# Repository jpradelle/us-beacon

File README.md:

# Ultrasonic indoor positioning system
This project contains electronic card design and software to build an indoor 2D positioning system based on ultrasonic 
emitters and receivers with Time Difference Of Arrival (TDOA) algorithm to determine position.

## Context
This project has been made during French Robotic Cup which takes place in european Eurobot contest. During this contest,
2 teams are playing one against the other, with one or two bots, to achieve some objectives, on a game table of 2 per 3
meters. Bots must not enter in collision with other team bots, purpose of this project is to determine quite precisely
position of 2 opponent bots.

Contest rules allow to place 3 fixed beacons on dedicated table places which will be called receivers, and a 
80mm\*80mm\*80mm beacon on each opponent bot which will be called emitters.

See [contest rules](doc/E2017_Rules_EN.pdf) for more details.

### Extra considerations
* Due to intensive usage of 40kHz ultrasonic modules by other teams, we avoided use of 40kHz frequency.
* To avoid possible interference with other teams, a sort of "modulation" have been implemented.
* Using low frequency ultrasonic transceivers and receivers allow to emit/receive on a wide angle.

## Principle
An emitter is placed on opponent bot, emitter will emit every 75ms a signal over 360°. One of the three fixed receivers
will receive the signal first at time reference T. Due to slow speed of sound, the 2nd receives a bit later at T + dt1,
and the 3rd later next at T + dt2. Knowing speed of sound, dt1 and dt2 can be converted to distance dr1 and dr2. With
only dr1 and dr2 and a Time Difference Of Arrival (TDOA) algorithm, we can compute position of emitter on a plan.

R is unknown, only dr1 and dr2 are determined by the system.

## System accuracy
TODO

## Architecture
Project is made of following parts.

### 2 emitters
One working with 25kHz frequency, one with 32.8kHz frequency. Emitters are made of:
* 1 9V battery
* 1 ATtiny45 microcontroller for pulse generation
* 4 ultrasonic transceivers
* some electronic for power supply, H bridge to run transceivers, ...

### 3 receivers
Each receiver beacon is made with one cards to receive 25kHz another one to receive 32.8kHz signals with 2 or 3
ultrasonic receivers.

Each ultrasonic receiver is made of
* 1 ultrasonic receiver
* 1 4 channels TLO74CN Operational Amplifier
* Some resistors, capacitors and schottky diodes for signal amplification and filtering
* 1 ATtiny45 for reading analog input and building a simple HIGH signal when ultrasonic signal is received

It contains also a power card which ensure different power conversions and aggregate demodulated signals from receivers,
made of:
* 2 9V battery
* 1 12V NCP1117DT12RKG convertor
* 1 5V R-78E5.0-0.5 convertor
* 1 3.3 LP2950ACDT-3.3RG convertor (for receiver beacon 1 only)
* Few connectors

#### Receiver 1
Contains 1 power card, 1 card with 2 receiver channels of 25kHz and 1 card with 2 receiver channels of 32.8kHz.

It also contains 1 RF card, which receive all numerical signals produced by receivers channels, compute TDOA algorithm
and send position by serial to RF module. It is made of:
* 1 Teensy 3.2 micro controller
* 1 RFBee (or 1 ESP8266, extra adaptor card needed)
* Few 3.3V zener diodes and schottky diodes
* Few connectors

#### Receiver 2
Contains 1 power card, 1 card with 2 receiver channels of 25kHz and 1 card with 2 receiver channels of 32.8kHz.

#### Receiver 3
Contains 1 power card, 1 card with 3 receiver channels of 25kHz and 1 card with 3 receiver channels of 32.8kHz.

## Folder structure of project
### Simulation
[simu](simu) folder contains some simulations for testing different TOA and TDOA algorithms.
See [simu/README.md](simu/README.md) for more details of algorithms performances.

### Electronics
[elec](elec) folder contains electronic designs of one 25kHz emitter, one 32.8kHz emitter, 3 receivers of 25kHz and
32.8kHz, and other power cards. See [elec/README.md](elec/README.md) for more information.

### Code
[code](code) folder contains code of all microcontroller used in this project. See [code/README.md](code/README.md) for
more information.

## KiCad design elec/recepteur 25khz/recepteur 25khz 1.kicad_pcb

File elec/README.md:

# Electronic
This folder contains needed electronics schema made with Kicad software for building working solution for 2 bots
positioning.

## Kicad projects
### 25kHz emitter
Electronic schematics and PCB drawings are made in [emetteur 25khz](emetteur%2025khz) project.

PDF schematics [here](../doc/elec/25khz_emitter_schematics.pdf)

### 32.8kHz emitter
Electronic schematics and PCB drawings are made in [emetteur 32khz](emetteur%2032khz) project.

PDF schematics [here](../doc/elec/32khz_emitter_schematics.pdf)

### 3 sets of 25kHz receivers
Electronic schematics and PCB drawings are made in [recepteur 25khz](recepteur%2025khz) project.

PDF schematics [here](../doc/elec/25khz_receiver_schematics.pdf)

Project contains stuff for building 2 fixed receiving beacons made of 2 ultrasonic receivers and 1 fixed receiving
beacon made of 3 ultrasonic receivers.

This projects contains other cards, see after.

### 3 sets of 32.8kHz receivers
Electronic schematics and PCB drawings are made in [recepteur 32khz](recepteur%2032khz) project.

PDF schematics [here](../doc/elec/32khz_receiver_schematics.pdf)

Project contains stuff for building 2 fixed receiving beacons made of 2 ultrasonic receivers and 1 fixed receiving
beacon made of 3 ultrasonic receivers.

### 3 power cards
Electronic schematics and PCB drawings are made in [recepteur 25khz](recepteur%2025khz) project.

Those 3 power cards are made for powering receiving cards and aggregating receiving cards signal to output them on one
connector.

### RF card
Electronic schematics and PCB drawings are made in [recepteur 25khz](recepteur%2025khz) project.

This RF card made for running TDOA algorithm with signals given from 3 power cards on a teensy microcontroller, found
position is expected to be transmitted by serial to RF card.

## Bill Of Material
### 25kHz emitter
| Item         | Qty | Reference(s)                                                            | RadioSpares ref    |
|--------------|-----|-------------------------------------------------------------------------|--------------------|
| 100n         | 1   | C1                                                                      | 264-4416           |
| LED          | 1   | D1                                                                      |                    |
| ATTINY45-P   | 1   | IC1                                                                     | 696-2614           |
| CONN_2       | 5   | P1, P3, P4, P5, P6                                                      | 163-5303, 163-5305 |
| 2N3904       | 8   | Q1, Q4, Q5, Q7, Q9, Q12, Q14, Q16                                       | 739-0397           |
| 2N3906       | 8   | Q2, Q3, Q6, Q8, Q10, Q11, Q13, Q15                                      | 739-0375           |
| 22k          | 16  | R1, R2, R4, R5, R7, R8, R9, R10, R11, R12, R16, R17, R18, R19, R20, R21 | 740-9016           |
| 1k           | 5   | R3, R6, R13, R14, R15                                                   | 740-8971           |
| 10k          | 1   | R22                                                                     | 740-9072           |
| R-78E5.0-0.5 | 1   | REGUL1                                                                  | 757-7239           |
| SWITCH       | 1   | U1                                                                      | 734-7315           |

+ 4 25kHz Ultrasonic transmitters

### 32.8kHz emitter
| Item         | Qty | Reference(s)                                                            | RadioSpares ref    |
|--------------|-----|-------------------------------------------------------------------------|--------------------|
| 100n         | 1   | C1                                                                      | 264-4416           |
| LED          | 1   | D1                                                                      |                    |
| ATTINY45-P   | 1   | IC1                                                                     | 696-2614           |
| CONN_2       | 5   | P1, P3, P4, P5, P6                                                      | 163-5303, 163-5305 |
| 2N3904       | 8   | Q1, Q4, Q5, Q7, Q9, Q12, Q14, Q16                                       | 739-0397           |
| 2N3906       | 8   | Q2, Q3, Q6, Q8, Q10, Q11, Q13, Q15                                      | 739-0375           |
| 22k          | 16  | R1, R2, R4, R5, R7, R8, R9, R10, R11, R12, R16, R17, R18, R19, R20, R21 | 740-9016           |
| 1k           | 5   | R3, R6, R13, R14, R15                                                   | 740-8971           |
| 10k          | 1   | R22                                                                     | 740-9072           |
| R-78E5.0-0.5 | 1   | REGUL1                                                                  | 757-7239           |
| SWITCH       | 1   | U1                                                                      | 734-7315           |

+ 4 32.8kHz Ultrasonic transmitters

### 25kHz receivers + power cards + RF card
| Value            | Qty | Reference(s)                                                                                                                                                                                            | RadioSpares ref    |
|------------------|-----|---------------------------------------------------------------------------------------------------------------------------------------------------------------------------------------------------------|--------------------|
| 10n              | 14  | C1, C5, C12, C16, C23, C27, C34, C38, C45, C49, C56, C60, C67, C71                                                                                                                                      | 264-4371           |
| 470p             | 14  | C2, C8, C13, C19, C24, C30, C35, C41, C46, C52, C57, C63, C68, C74                                                                                                                                      | 264-4315           |
| 47n              | 14  | C3, C4, C14, C15, C25, C26, C36, C37, C47, C48, C58, C59, C69, C70                                                                                                                                      | 147-998            |
| 100n             | 21  | C6, C7, C11, C17, C18, C22, C28, C29, C33, C39, C40, C44, C50, C51, C55, C61, C62, C66, C72, C73, C77                                                                                                   | 264-4416           |
| 1n               | 14  | C9, C10, C20, C21, C31, C32, C42, C43, C53, C54, C64, C65, C75, C76                                                                                                                                     | 264-4337           |
| 10µ              | 6   | C78, C79, C80, C81, C82, C83                                                                                                                                                                            | 440-6553           |
| 1µ               | 1   | C84                                                                                                                                                                                                     |                    |
| DIODESCH         | 42  | D1, D2, D3, D4, D5, D6, D7, D8, D9, D10, D11, D12, D13, D14, D15, D16, D17, D18, D19, D20, D21, D22, D23, D24, D25, D26, D27, D28, D39, D41, D43, D45, D47, D49, D51, D53, D55, D57, D59, D61, D63, D65 | 743-5894           |
| LED              | 10  | D29, D30, D31, D32, D33, D34, D35, D36, D37, D38                                                                                                                                                        |                    |
| ZENER            | 14  | D40, D42, D44, D46, D48, D50, D52, D54, D56, D58, D60, D62, D64, D66                                                                                                                                    | 710-4216           |
| ATTINY45-P       | 7   | IC1, IC2, IC3, IC4, IC5, IC6, IC7                                                                                                                                                                       | 696-2614           |
| TEENSY           | 1   | IC8                                                                                                                                                                                                     |                    |
| CONN_3           | 1   | K1                                                                                                                                                                                                      | 163-5303, 163-5305 |
| CONN_6           | 6   | P1, P4, P5, P8, P10, P17                                                                                                                                                                                | 163-5303, 163-5305 |
| CONN_2           | 6   | P2, P3, P6, P7, P12, P13                                                                                                                                                                                | 163-5303, 163-5305 |
| CONN_5           | 2   | P9, P19                                                                                                                                                                                                 | 163-5303, 163-5305 |
| CONN_7           | 7   | P11, P14, P15, P16, P18, P20, P21                                                                                                                                                                       | 163-5303, 163-5305 |
| CONN_4           | 1   | P22                                                                                                                                                                                                     | 163-5303, 163-5305 |
| 1k               | 21  | R1, R2, R5, R11, R12, R13, R14, R17, R27, R33, R34, R37, R45, R46, R49, R55, R56, R59, R65, R66, R69                                                                                                    | 740-8971           |
| 10k              | 37  | R3, R4, R8, R15, R16, R20, R23, R24, R25, R26, R30, R35, R36, R40, R43, R44, R47, R48, R52, R57, R58, R62, R67, R68, R72, R75, R76, R77, R78, R79, R80, R81, R82, R83, R84, R85, R86                    | 740-9072           |
| 47k              | 28  | R6, R7, R9, R10, R18, R19, R21, R22, R28, R29, R31, R32, R38, R39, R41, R42, R50, R51, R53, R54, R60, R61, R63, R64, R70, R71, R73, R74                                                                 | 740-9035           |
| 2.2k             | 14  | R87, R88, R89, R90, R91, R92, R93, R94, R95, R96, R97, R98, R99, R100                                                                                                                                   | 810-1750           |
| RFBEE            | 1   | RF1                                                                                                                                                                                                     |                    |
| TL074            | 7   | U1, U2, U3, U4, U9, U10, U11                                                                                                                                                                            | 302-621            |
| R-78E5.0-0.5     | 3   | U5, U7, U12                                                                                                                                                                                             | 757-7239           |
| NCP1117DT12RKG   | 3   | U6, U8, U13                                                                                                                                                                                             | 518-8341           |
| SWITCH           | 3   | U14, U15, U16                                                                                                                                                                                           | 734-7315           |
| LP2950ACDT-3.3RG | 1   | U17                                                                                                                                                                                                     | 805-1416           |
| ULTRASON         | 7   | US1, US2, US3, US4, US5, US6, US7                                                                                                                                                                       |                    |

### 32.8kHz receivers
| Value      | Qty | Reference(s)                                                                                                                            | RadioSpares ref    |
|------------|-----|-----------------------------------------------------------------------------------------------------------------------------------------|--------------------|
| 6.8n       | 14  | C1, C5, C12, C16, C23, C27, C34, C38, C45, C49, C56, C60, C67, C71                                                                      |                    |
| 220p       | 14  | C2, C8, C13, C19, C24, C30, C35, C41, C46, C52, C57, C63, C68, C74                                                                      | 264-4309           |
| 47n        | 14  | C3, C4, C14, C15, C25, C26, C36, C37, C47, C48, C58, C59, C69, C70                                                                      | 147-998            |
| 100n       | 21  | C6, C7, C11, C17, C18, C22, C28, C29, C33, C39, C40, C44, C50, C51, C55, C61, C62, C66, C72, C73, C77                                   | 264-4416           |
| 1n         | 7   | C9, C20, C31, C42, C53, C64, C75                                                                                                        | 264-4337           |
| 2.2n       | 7   | C10, C21, C32, C43, C54, C65, C76                                                                                                       | 264-4359           |
| DIODESCH   | 28  | D1, D2, D3, D4, D5, D6, D7, D8, D9, D10, D11, D12, D13, D14, D15, D16, D17, D18, D19, D20, D21, D22, D23, D24, D25, D26, D27, D28       | 743-5894           |
| LED        | 7   | D29, D30, D31, D32, D33, D34, D35                                                                                                       |                    |
| ATTINY45-P | 7   | IC1, IC2, IC3, IC4, IC5, IC6, IC7                                                                                                       | 696-2614           |
| CONN_6     | 2   | P4, P5                                                                                                                                  | 163-5303, 163-5305 |
| CONN_7     | 1   | P11                                                                                                                                     | 163-5303, 163-5305 |
| 1k         | 21  | R1, R2, R5, R11, R12, R13, R14, R17, R27, R33, R34, R37, R45, R46, R49, R55, R56, R59, R65, R66, R69                                    | 740-8971           |
| 22k        | 14  | R3, R8, R15, R20, R25, R30, R35, R40, R47, R52, R57, R62, R67, R72                                                                      | 740-9016           |
| 6.8k       | 7   | R4, R16, R26, R36, R48, R58, R68                                                                                                        | 810-1889           |
| 47k        | 28  | R6, R7, R9, R10, R18, R19, R21, R22, R28, R29, R31, R32, R38, R39, R41, R42, R50, R51, R53, R54, R60, R61, R63, R64, R70, R71, R73, R74 | 740-9035           |
| 10k        | 7   | R77, R78, R79, R80, R81, R82, R83                                                                                                       | 740-9072           |
| TL074      | 7   | U1, U2, U3, U4, U9, U10, U11                                                                                                            | 302-621            |
| ULTRASON   | 7   | US1, US2, US3, US4, US5, US6, US7                                                                                                       |                    |

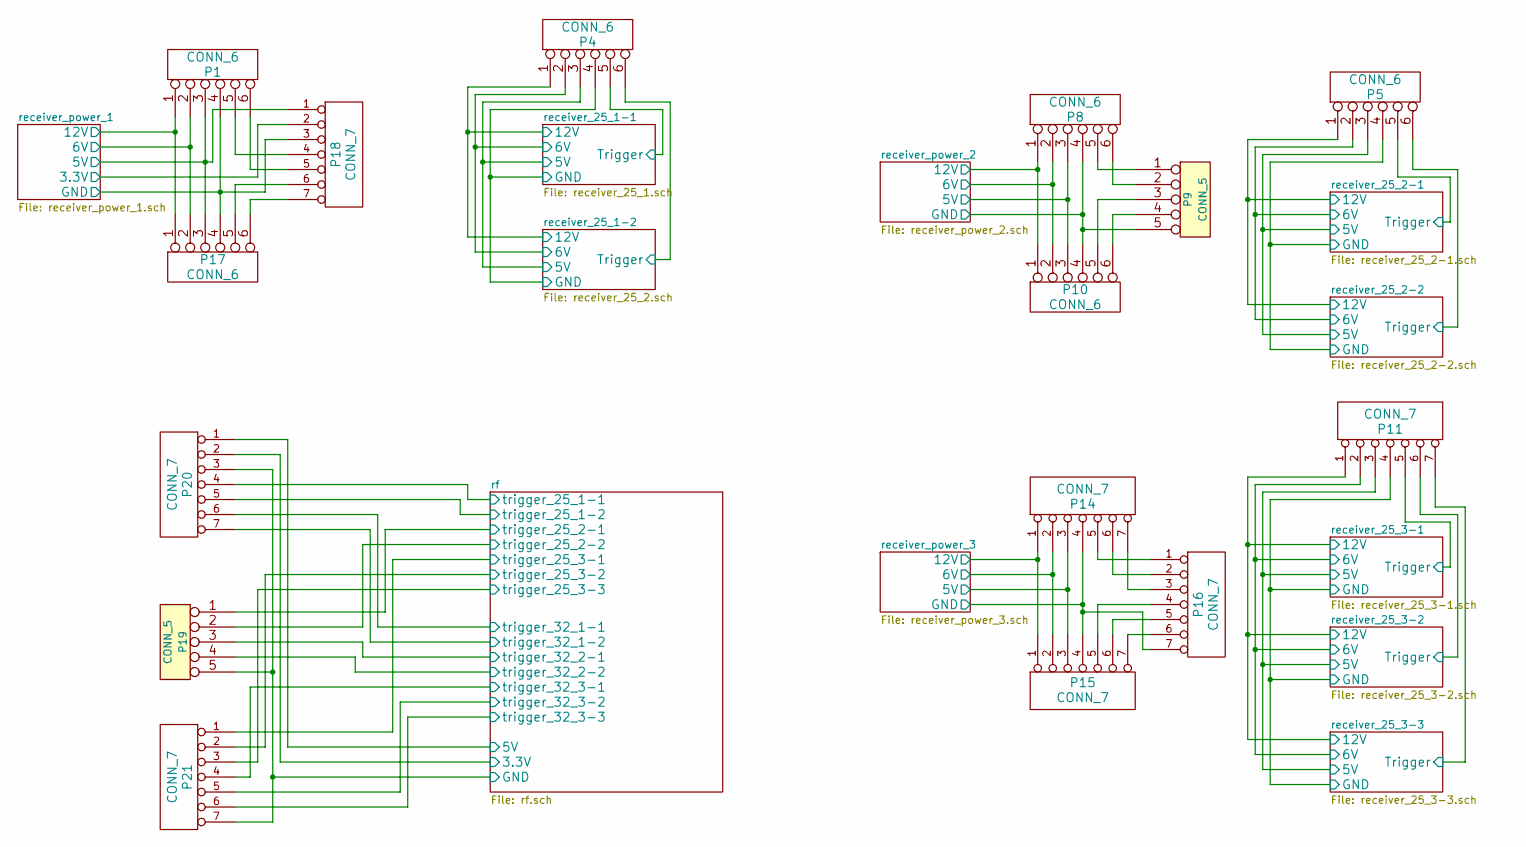
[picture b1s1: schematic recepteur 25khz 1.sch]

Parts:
P1, P4, P5, P8, P10, P17: CONN_6
P9, P19: CONN_5
P11, P14, P15, P16, P18, P20, P21: CONN_7

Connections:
/receiver_25_1-1/5V: P4.3; also elsewhere on the board
/receiver_25_1-1/6V: P4.2; also elsewhere on the board
/receiver_25_1-1/12V: P4.1; also elsewhere on the board
/receiver_25_1-1/GND: P4.4; also elsewhere on the board
/receiver_25_1-1/Trigger: P4.5; also elsewhere on the board
/receiver_25_1-2/Trigger: P4.6; also elsewhere on the board
/receiver_25_2-1/5V: P5.3; also elsewhere on the board
/receiver_25_2-1/6V: P5.2; also elsewhere on the board
/receiver_25_2-1/12V: P5.1; also elsewhere on the board
/receiver_25_2-1/GND: P5.4; also elsewhere on the board
/receiver_25_2-1/Trigger: P5.5; also elsewhere on the board
/receiver_25_2-2/Trigger: P5.6; also elsewhere on the board
/receiver_25_3-1/5V: P11.3; also elsewhere on the board
/receiver_25_3-1/6V: P11.2; also elsewhere on the board
/receiver_25_3-1/12V: P11.1; also elsewhere on the board
/receiver_25_3-1/GND: P11.4; also elsewhere on the board
/receiver_25_3-1/Trigger: P11.5; also elsewhere on the board
/receiver_25_3-2/Trigger: P11.6; also elsewhere on the board
/receiver_25_3-3/Trigger: P11.7; also elsewhere on the board
/receiver_power_1/3.3V: P18.2; also elsewhere on the board
/receiver_power_1/5V: P1.3, P17.3, P18.1; also elsewhere on the board
/receiver_power_1/6V: P1.2, P17.2; also elsewhere on the board
/receiver_power_1/12V: P1.1, P17.1; also elsewhere on the board
/receiver_power_1/GND: P1.4, P17.4, P18.3; also elsewhere on the board
/receiver_power_2/5V: P8.3, P10.3; also elsewhere on the board
/receiver_power_2/6V: P8.2, P10.2; also elsewhere on the board
/receiver_power_2/12V: P8.1, P10.1; also elsewhere on the board
/receiver_power_2/GND: P8.4, P9.5, P10.4; also elsewhere on the board
/receiver_power_3/5V: P14.3, P15.3; also elsewhere on the board
/receiver_power_3/6V: P14.2, P15.2; also elsewhere on the board
/receiver_power_3/12V: P14.1, P15.1; also elsewhere on the board
/receiver_power_3/GND: P14.4, P15.4, P16.7; also elsewhere on the board
/rf/3.3V: P20.2; also elsewhere on the board
/rf/5V: P20.1; also elsewhere on the board
/rf/GND: P19.5, P20.3, P21.7; also elsewhere on the board
/rf/trigger_25_1-1: P20.4; also elsewhere on the board
/rf/trigger_25_1-2: P20.5; also elsewhere on the board
/rf/trigger_25_2-1: P19.1; also elsewhere on the board
/rf/trigger_25_2-2: P19.2; also elsewhere on the board
/rf/trigger_25_3-1: P21.1; also elsewhere on the board
/rf/trigger_25_3-2: P21.2; also elsewhere on the board
/rf/trigger_25_3-3: P21.3; also elsewhere on the board
/rf/trigger_32_1-1: P20.6; also elsewhere on the board
/rf/trigger_32_1-2: P20.7; also elsewhere on the board
/rf/trigger_32_2-1: P19.3; also elsewhere on the board
/rf/trigger_32_2-2: P19.4; also elsewhere on the board
/rf/trigger_32_3-1: P21.4; also elsewhere on the board
/rf/trigger_32_3-2: P21.5; also elsewhere on the board
/rf/trigger_32_3-3: P21.6; also elsewhere on the board
unnamed: P1.5, P18.4
unnamed: P1.6, P18.5
unnamed: P8.5, P9.1
unnamed: P8.6, P9.2
unnamed: P9.3, P10.5
unnamed: P9.4, P10.6
unnamed: P14.5, P16.1
unnamed: P14.6, P16.2
unnamed: P14.7, P16.3
unnamed: P15.5, P16.4
unnamed: P15.6, P16.5
unnamed: P15.7, P16.6
unnamed: P17.5, P18.6
unnamed: P17.6, P18.7

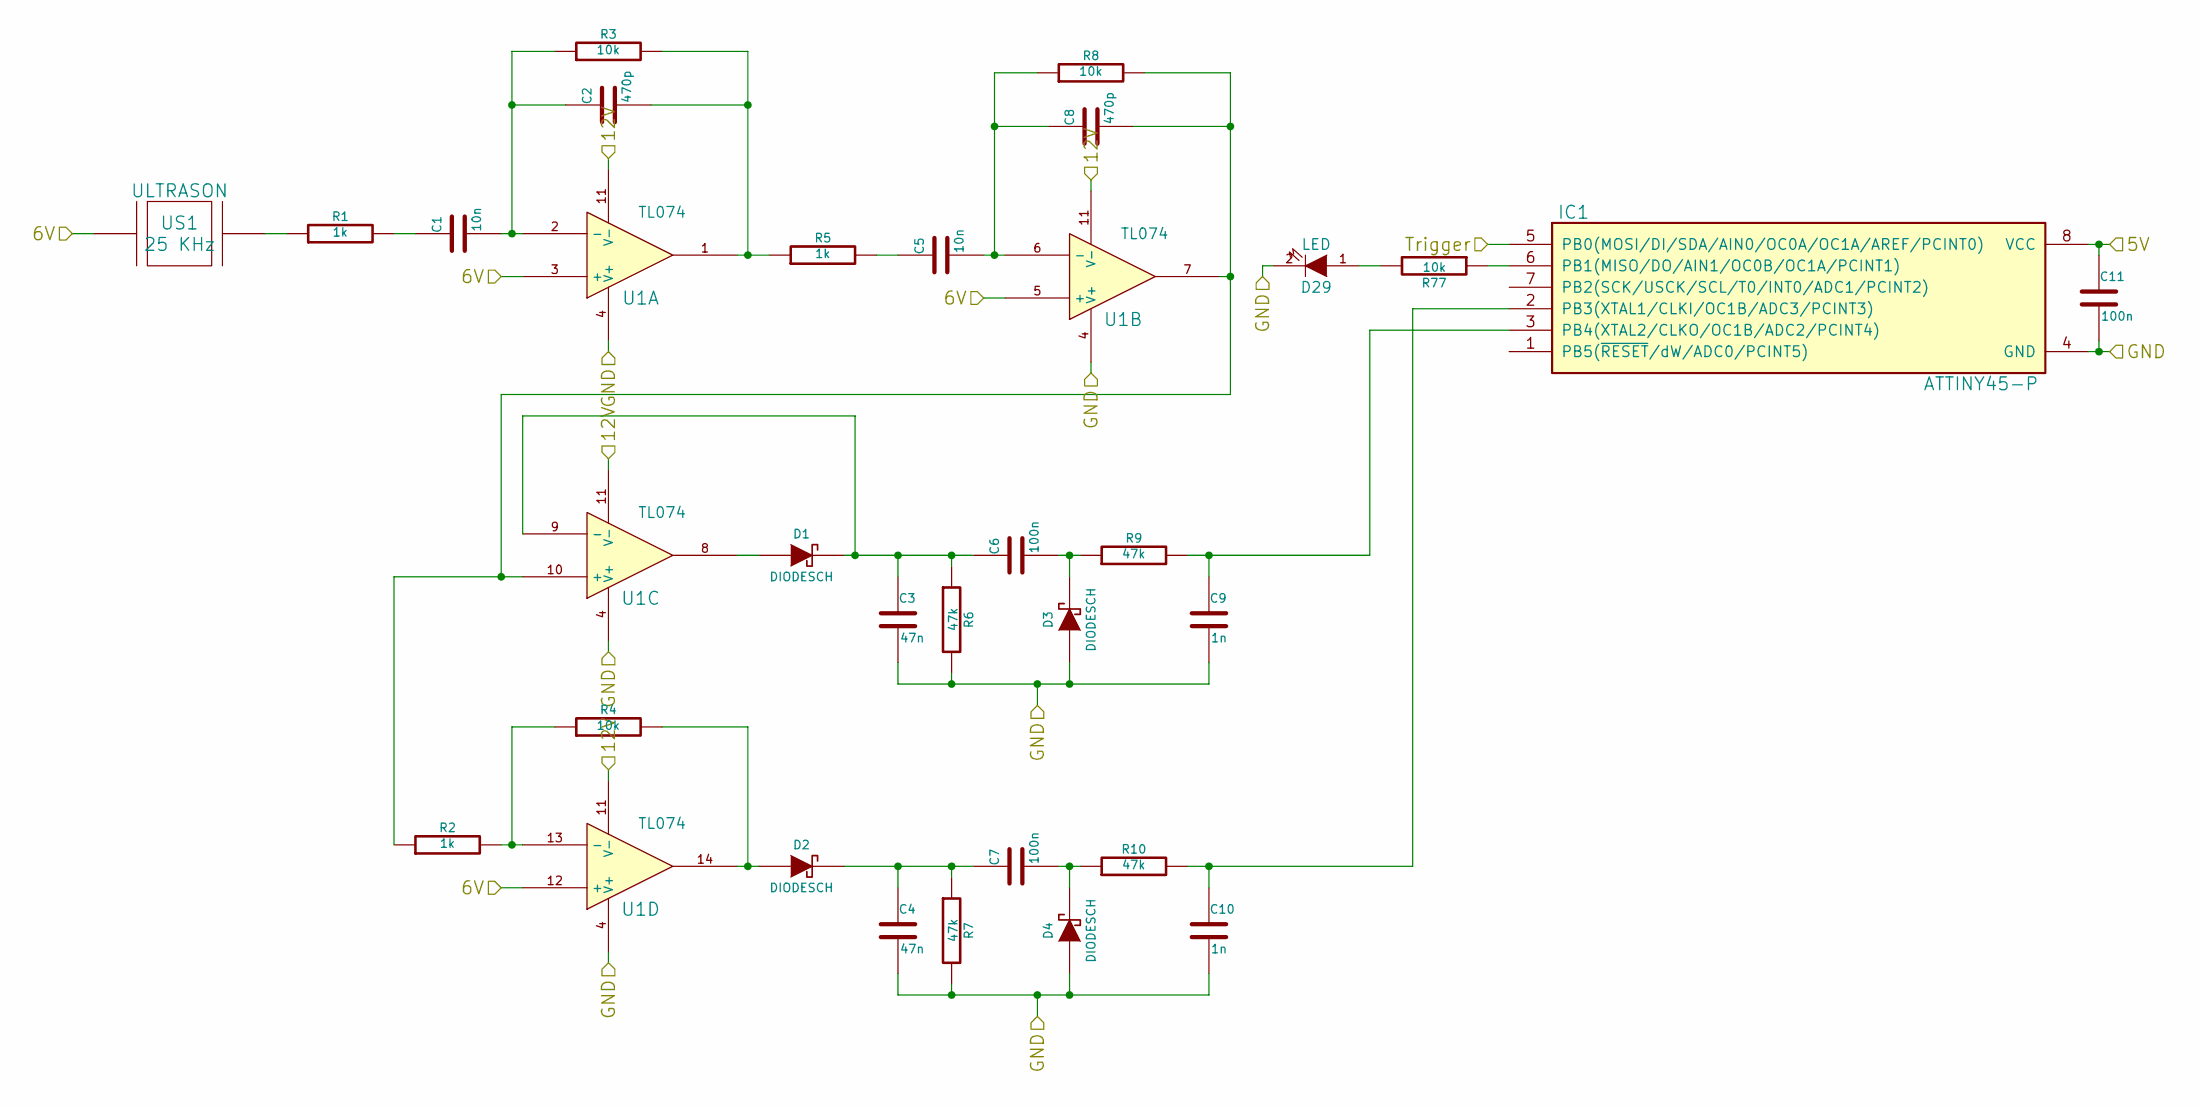
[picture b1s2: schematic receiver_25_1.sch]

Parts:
C1, C5: 10n
C2, C8: 470p
C3, C4: 47n
C6, C7, C11: 100n
C9, C10: 1n
D1, D2, D3, D4: DIODESCH
D29: LED
IC1: ATTINY45-P; DIP8
R1, R2, R5: 1k
R3, R4, R8, R77: 10k
R6, R7, R9, R10: 47k
U1: TL074
US1: ULTRASON

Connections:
/receiver_25_1-1/5V: C11.1, IC1.8 (VCC); also elsewhere on the board
/receiver_25_1-1/6V: U1.3 (+), U1.5 (+), U1.12 (+), US1.1; also elsewhere on the board
/receiver_25_1-1/12V: U1.11 (V-); also elsewhere on the board
/receiver_25_1-1/GND: C3.2, C4.2, C9.2, C10.2, C11.2, D3.1 (A), D4.1 (A), D29.2 (K), IC1.4 (GND), R6.2, R7.2, U1.4 (V+); also elsewhere on the board
/receiver_25_1-1/Trigger: IC1.5 (PB0(MOSI/DI/SDA/AIN0/OC0A/OC1A/AREF/PCI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); also elsewhere on the board
unnamed: C1.1, R1.2
unnamed: C1.2, C2.1, R3.1, U1.2 (-)
unnamed: C2.2, R3.2, R5.1, U1.1
unnamed: C3.1, C6.1, D1.2 (K), R6.1, U1.9 (-)
unnamed: C4.1, C7.1, D2.2 (K), R7.1
unnamed: C5.1, R5.2
unnamed: C5.2, C8.1, R8.1, U1.6 (-)
unnamed: C6.2, D3.2 (K), R9.1
unnamed: C7.2, D4.2 (K), R10.1
unnamed: C8.2, R2.1, R8.2, U1.7, U1.10 (+)
unnamed: C9.1, IC1.3 (PB4(XTAL2/CLKO/OC1B/ADC2/PCINT4)), R9.2
unnamed: C10.1, IC1.2 (PB3(XTAL1/CLKI/OC1B/ADC3/PCINT3)), R10.2
unnamed: D1.1 (A), U1.8
unnamed: D2.1 (A), R4.2, U1.14
unnamed: D29.1 (A), R77.2
unnamed: IC1.6 (PB1(MISO/DO/AIN1/OC0B/OC1A/PCINT1)), R77.1
unnamed: R1.1, US1.2
unnamed: R2.2, R4.1, U1.13 (-)

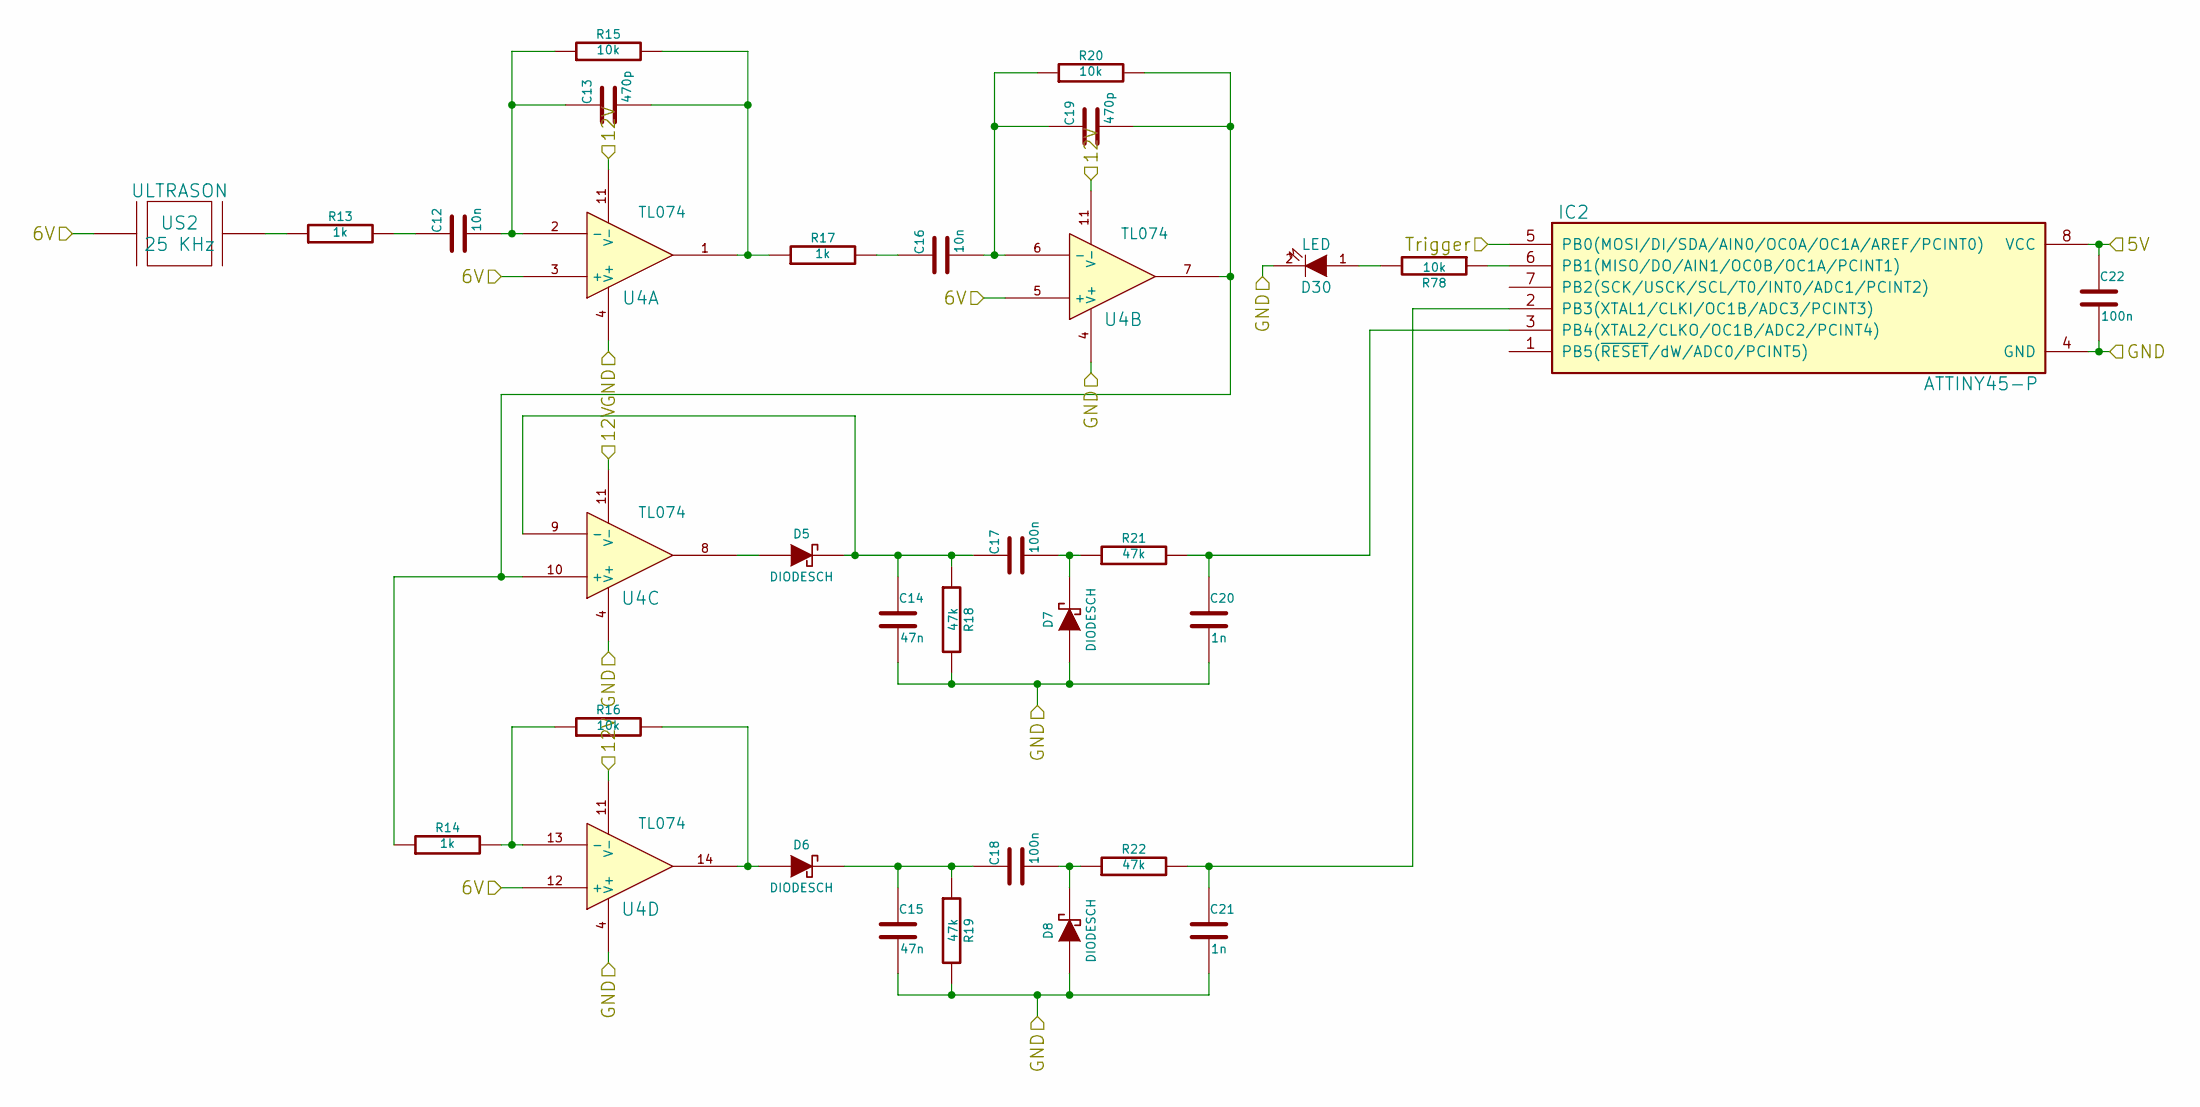
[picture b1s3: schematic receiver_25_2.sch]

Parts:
C12, C16: 10n
C13, C19: 470p
C14, C15: 47n
C17, C18, C22: 100n
C20, C21: 1n
D5, D6, D7, D8: DIODESCH
D30: LED
IC2: ATTINY45-P; DIP8
R13, R14, R17: 1k
R15, R16, R20, R78: 10k
R18, R19, R21, R22: 47k
U4: TL074
US2: ULTRASON

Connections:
/receiver_25_1-1/5V: C22.1, IC2.8 (VCC); also elsewhere on the board
/receiver_25_1-1/6V: U4.3 (+), U4.5 (+), U4.12 (+), US2.1; also elsewhere on the board
/receiver_25_1-1/12V: U4.11 (V-); also elsewhere on the board
/receiver_25_1-1/GND: C14.2, C15.2, C20.2, C21.2, C22.2, D7.1 (A), D8.1 (A), D30.2 (K), IC2.4 (GND), R18.2, R19.2, U4.4 (V+); also elsewhere on the board
/receiver_25_1-2/Trigger: IC2.5 (PB0(MOSI/DI/SDA/AIN0/OC0A/OC1A/AREF/PCI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); also elsewhere on the board
unnamed: C12.1, R13.2
unnamed: C12.2, C13.1, R15.1, U4.2 (-)
unnamed: C13.2, R15.2, R17.1, U4.1
unnamed: C14.1, C17.1, D5.2 (K), R18.1, U4.9 (-)
unnamed: C15.1, C18.1, D6.2 (K), R19.1
unnamed: C16.1, R17.2
unnamed: C16.2, C19.1, R20.1, U4.6 (-)
unnamed: C17.2, D7.2 (K), R21.1
unnamed: C18.2, D8.2 (K), R22.1
unnamed: C19.2, R14.1, R20.2, U4.7, U4.10 (+)
unnamed: C20.1, IC2.3 (PB4(XTAL2/CLKO/OC1B/ADC2/PCINT4)), R21.2
unnamed: C21.1, IC2.2 (PB3(XTAL1/CLKI/OC1B/ADC3/PCINT3)), R22.2
unnamed: D5.1 (A), U4.8
unnamed: D6.1 (A), R16.2, U4.14
unnamed: D30.1 (A), R78.2
unnamed: IC2.6 (PB1(MISO/DO/AIN1/OC0B/OC1A/PCINT1)), R78.1
unnamed: R13.1, US2.2
unnamed: R14.2, R16.1, U4.13 (-)

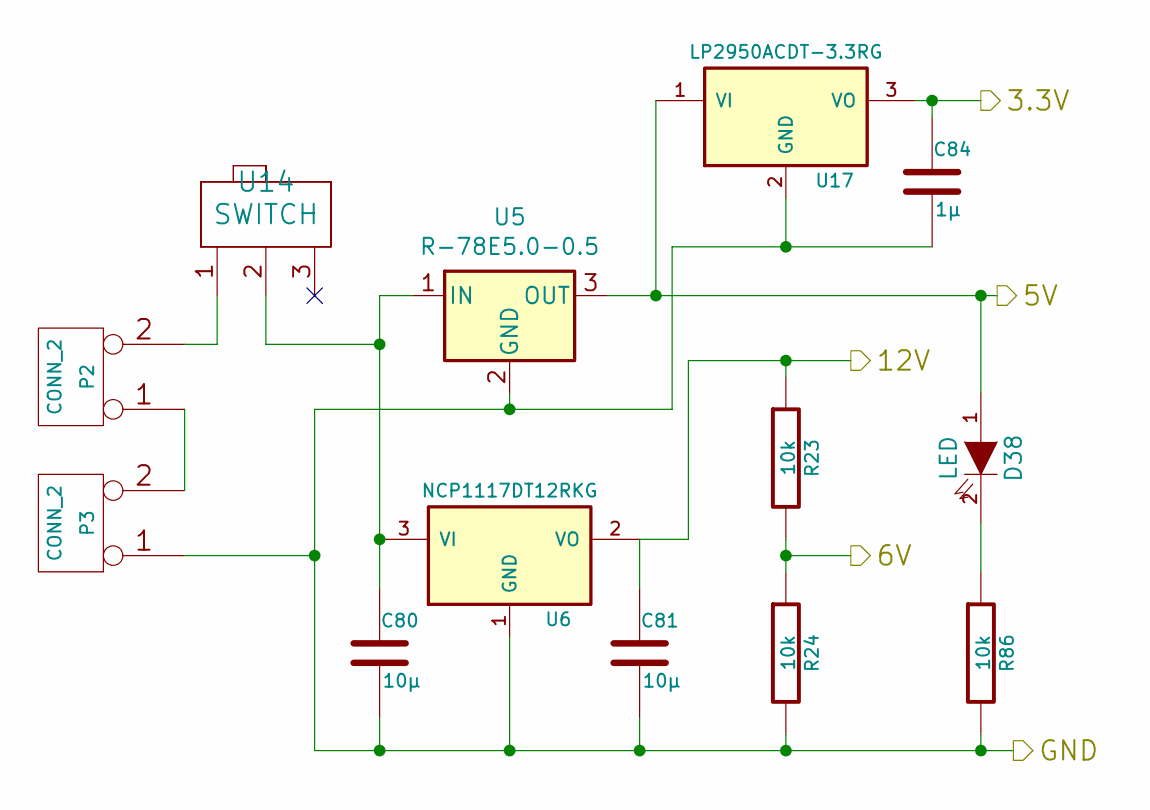
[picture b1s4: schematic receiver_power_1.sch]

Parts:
C80, C81: 10µ
C84: 1µ
D38: LED
P2, P3: CONN_2
R23, R24, R86: 10k
U5: R-78E5.0-0.5; Converter_DCDC_RECOM_R-78E-0.5_THT
U6: NCP1117DT12RKG
U14: SWITCH
U17: LP2950ACDT-3.3RG

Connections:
/receiver_power_1/3.3V: C84.1, U17.3 (VO); also elsewhere on the board
/receiver_power_1/5V: D38.1 (A), U5.3 (OUT), U17.1 (VI); also elsewhere on the board
/receiver_power_1/6V: R23.2, R24.1; also elsewhere on the board
/receiver_power_1/12V: C81.1, R23.1, U6.2 (VO); also elsewhere on the board
/receiver_power_1/GND: C80.2, C81.2, C84.2, P3.1, R24.2, R86.2, U5.2 (GND), U6.1 (GND), U17.2 (GND); also elsewhere on the board
unnamed: C80.1, U5.1 (IN), U6.3 (VI), U14.2
unnamed: D38.2 (K), R86.1
unnamed: P2.1, P3.2 (PM)
unnamed: P2.2 (PM), U14.1

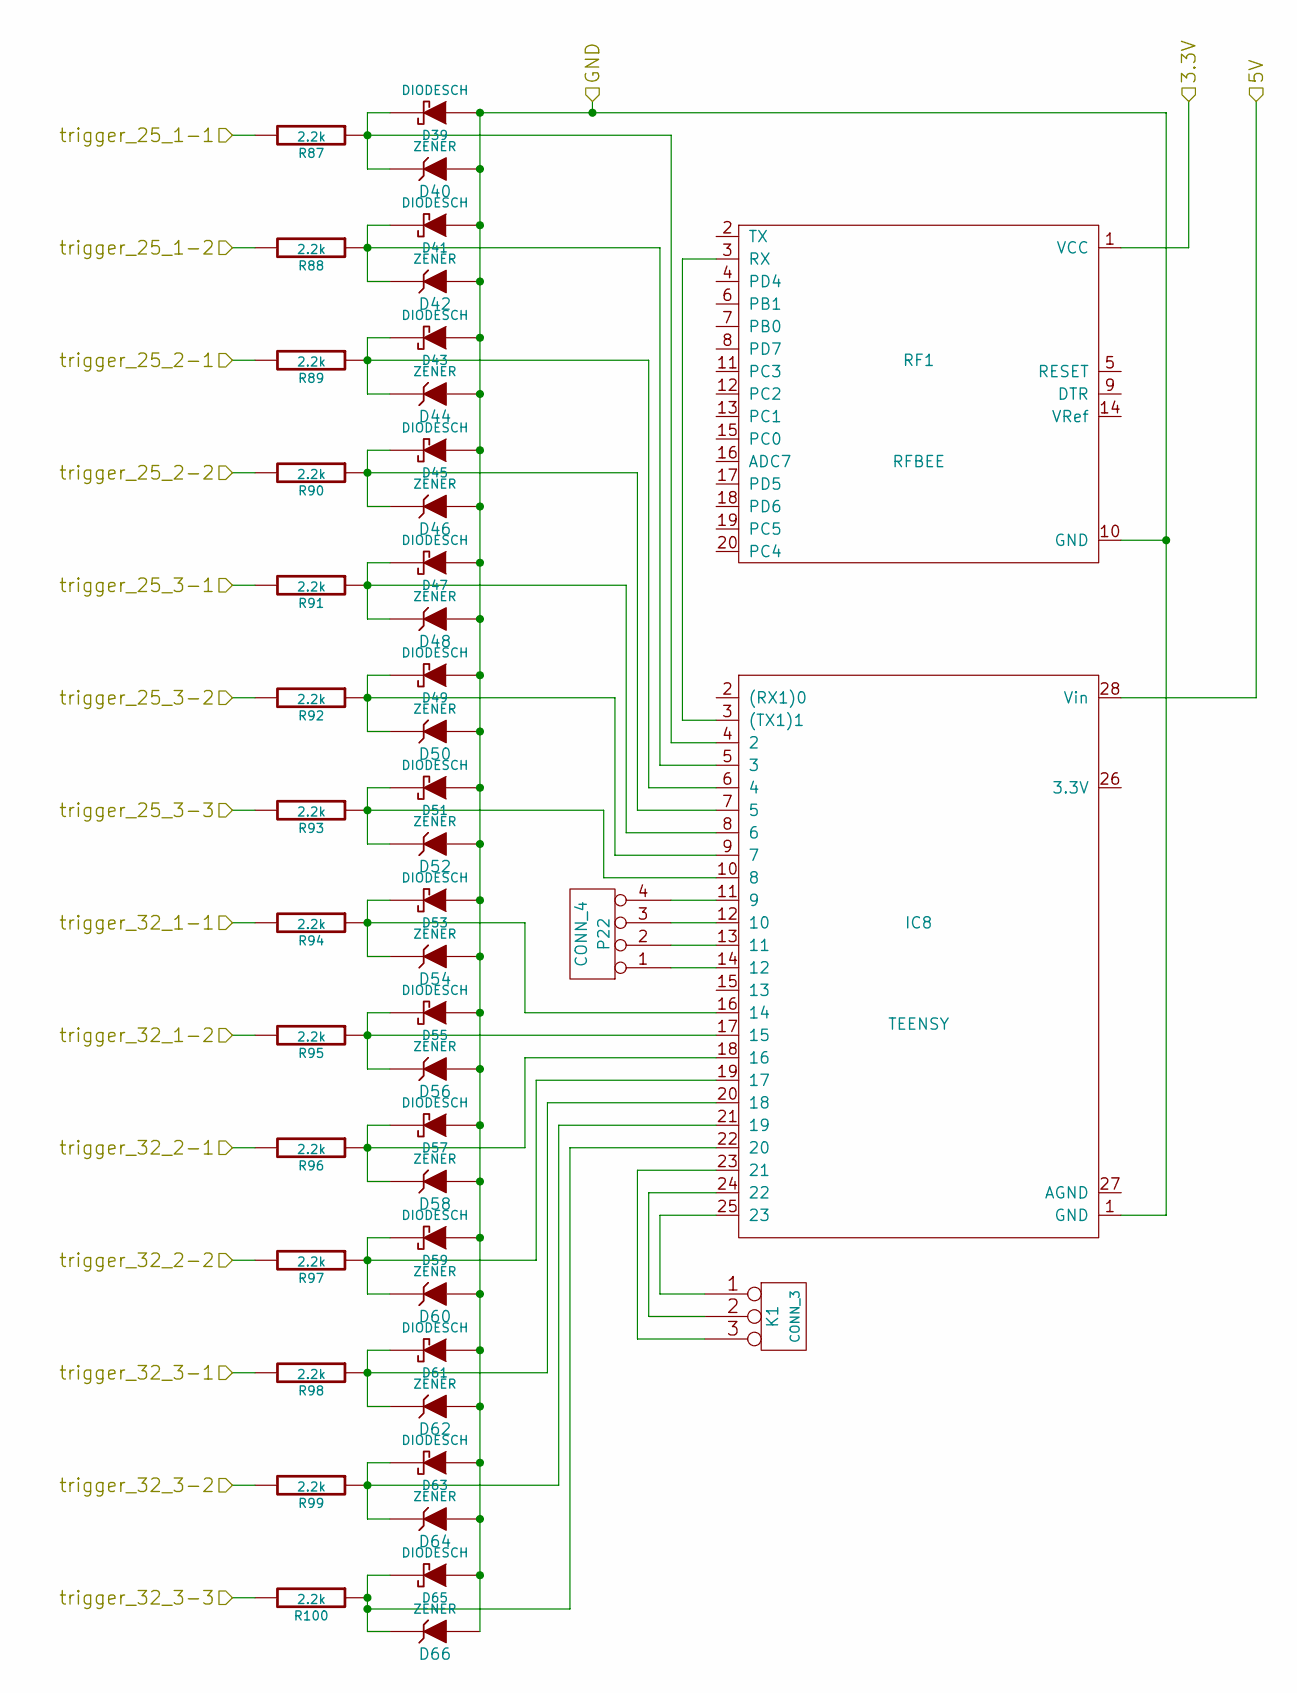
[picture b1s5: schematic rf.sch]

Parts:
D39, D41, D43, D45, D47, D49, D51, D53, D55, D57, D59, D61, D63, D65: DIODESCH
D40, D42, D44, D46, D48, D50, D52, D54, D56, D58, D60, D62, D64, D66: ZENER
IC8: TEENSY; Teensy
K1: CONN_3
P22: CONN_4
R87, R88, R89, R90, R91, R92, R93, R94, R95, R96, R97, R98, R99, R100: 2.2k
RF1: RFBEE; zigbee

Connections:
/rf/3.3V: RF1.1 (VCC); also elsewhere on the board
/rf/5V: IC8.28 (Vin); also elsewhere on the board
/rf/GND: D39.1 (A), D40.1 (A), D41.1 (A), D42.1 (A), D43.1 (A), D44.1 (A), D45.1 (A), D46.1 (A), D47.1 (A), D48.1 (A), D49.1 (A), D50.1 (A), D51.1 (A), D52.1 (A), D53.1 (A), D54.1 (A), D55.1 (A), D56.1 (A), D57.1 (A), D58.1 (A), D59.1 (A), D60.1 (A), D61.1 (A), D62.1 (A), D63.1 (A), D64.1 (A), D65.1 (A), D66.1 (A), IC8.1 (GND), RF1.10 (GND); also elsewhere on the board
/rf/trigger_25_1-1: R87.2; also elsewhere on the board
/rf/trigger_25_1-2: R88.2; also elsewhere on the board
/rf/trigger_25_2-1: R89.2; also elsewhere on the board
/rf/trigger_25_2-2: R90.2; also elsewhere on the board
/rf/trigger_25_3-1: R91.2; also elsewhere on the board
/rf/trigger_25_3-2: R92.2; also elsewhere on the board
/rf/trigger_25_3-3: R93.2; also elsewhere on the board
/rf/trigger_32_1-1: R94.2; also elsewhere on the board
/rf/trigger_32_1-2: R95.2; also elsewhere on the board
/rf/trigger_32_2-1: R96.2; also elsewhere on the board
/rf/trigger_32_2-2: R97.2; also elsewhere on the board
/rf/trigger_32_3-1: R98.2; also elsewhere on the board
/rf/trigger_32_3-2: R99.2; also elsewhere on the board
/rf/trigger_32_3-3: R100.2; also elsewhere on the board
unnamed: D39.2 (K), D40.2 (K), IC8.4 (2), R87.1
unnamed: D41.2 (K), D42.2 (K), IC8.5 (3), R88.1
unnamed: D43.2 (K), D44.2 (K), IC8.6 (4), R89.1
unnamed: D45.2 (K), D46.2 (K), IC8.7 (5), R90.1
unnamed: D47.2 (K), D48.2 (K), IC8.8 (6), R91.1
unnamed: D49.2 (K), D50.2 (K), IC8.9 (7), R92.1
unnamed: D51.2 (K), D52.2 (K), IC8.10 (8), R93.1
unnamed: D53.2 (K), D54.2 (K), IC8.16 (14), R94.1
unnamed: D55.2 (K), D56.2 (K), IC8.17 (15), R95.1
unnamed: D57.2 (K), D58.2 (K), IC8.18 (16), R96.1
unnamed: D59.2 (K), D60.2 (K), IC8.19 (17), R97.1
unnamed: D61.2 (K), D62.2 (K), IC8.20 (18), R98.1
unnamed: D63.2 (K), D64.2 (K), IC8.21 (19), R99.1
unnamed: D65.2 (K), D66.2 (K), IC8.22 (20), R100.1
unnamed: IC8.3 ((TX1)1), RF1.3 (RX)
unnamed: IC8.11 (9), P22.4
unnamed: IC8.12 (10), P22.3
unnamed: IC8.13 (11), P22.2
unnamed: IC8.14 (12), P22.1
unnamed: IC8.23 (21), K1.3
unnamed: IC8.24 (22), K1.2 (PM)
unnamed: IC8.25 (23), K1.1

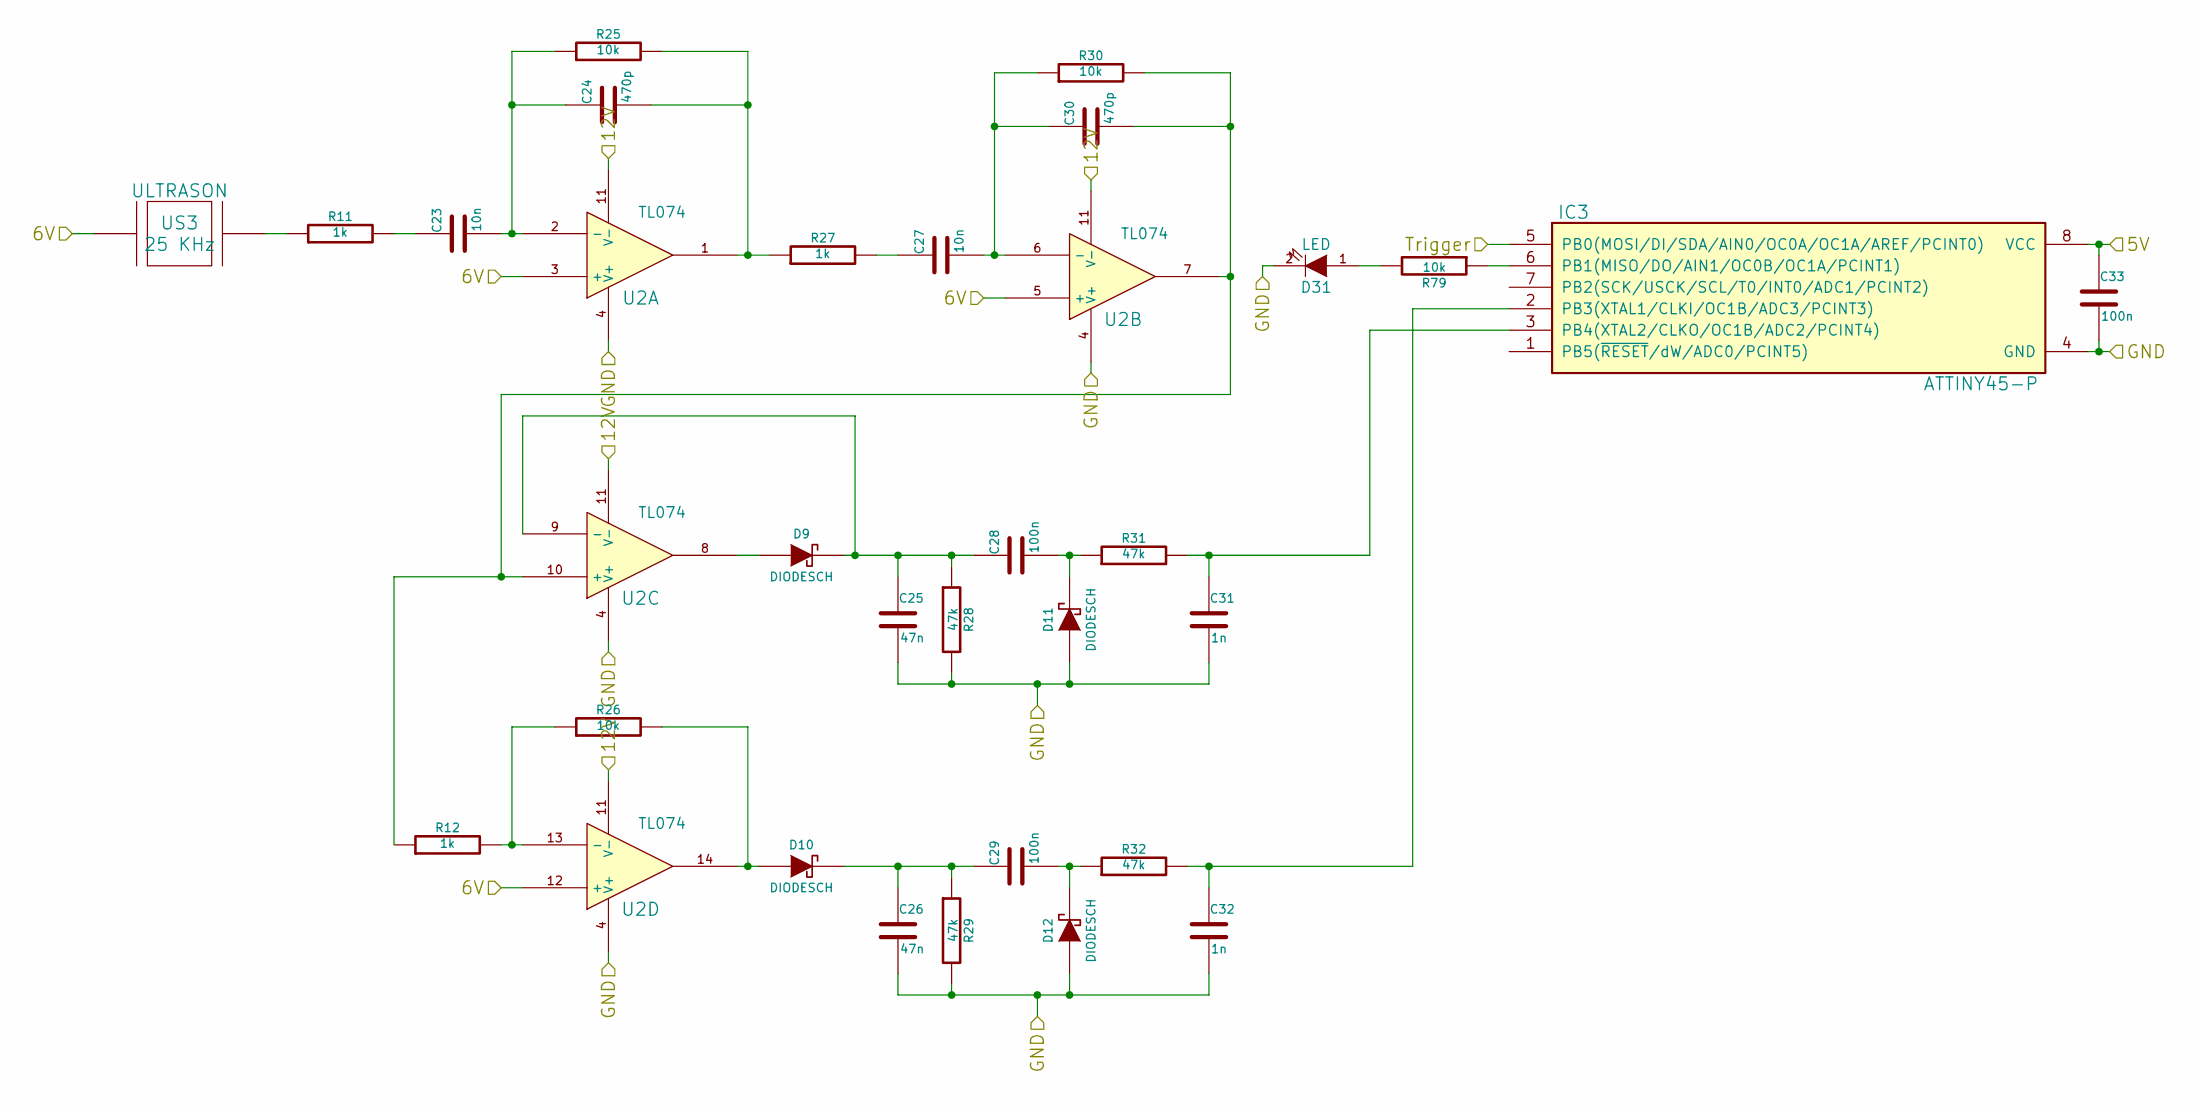
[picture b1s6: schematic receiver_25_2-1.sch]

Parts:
C23, C27: 10n
C24, C30: 470p
C25, C26: 47n
C28, C29, C33: 100n
C31, C32: 1n
D9, D10, D11, D12: DIODESCH
D31: LED
IC3: ATTINY45-P; DIP8
R11, R12, R27: 1k
R25, R26, R30, R79: 10k
R28, R29, R31, R32: 47k
U2: TL074
US3: ULTRASON

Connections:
/receiver_25_2-1/5V: C33.1, IC3.8 (VCC); also elsewhere on the board
/receiver_25_2-1/6V: U2.3 (+), U2.5 (+), U2.12 (+), US3.1; also elsewhere on the board
/receiver_25_2-1/12V: U2.11 (V-); also elsewhere on the board
/receiver_25_2-1/GND: C25.2, C26.2, C31.2, C32.2, C33.2, D11.1 (A), D12.1 (A), D31.2 (K), IC3.4 (GND), R28.2, R29.2, U2.4 (V+); also elsewhere on the board
/receiver_25_2-1/Trigger: IC3.5 (PB0(MOSI/DI/SDA/AIN0/OC0A/OC1A/AREF/PCI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); also elsewhere on the board
unnamed: C23.1, R11.2
unnamed: C23.2, C24.1, R25.1, U2.2 (-)
unnamed: C24.2, R25.2, R27.1, U2.1
unnamed: C25.1, C28.1, D9.2 (K), R28.1, U2.9 (-)
unnamed: C26.1, C29.1, D10.2 (K), R29.1
unnamed: C27.1, R27.2
unnamed: C27.2, C30.1, R30.1, U2.6 (-)
unnamed: C28.2, D11.2 (K), R31.1
unnamed: C29.2, D12.2 (K), R32.1
unnamed: C30.2, R12.1, R30.2, U2.7, U2.10 (+)
unnamed: C31.1, IC3.3 (PB4(XTAL2/CLKO/OC1B/ADC2/PCINT4)), R31.2
unnamed: C32.1, IC3.2 (PB3(XTAL1/CLKI/OC1B/ADC3/PCINT3)), R32.2
unnamed: D9.1 (A), U2.8
unnamed: D10.1 (A), R26.2, U2.14
unnamed: D31.1 (A), R79.2
unnamed: IC3.6 (PB1(MISO/DO/AIN1/OC0B/OC1A/PCINT1)), R79.1
unnamed: R11.1, US3.2
unnamed: R12.2, R26.1, U2.13 (-)
